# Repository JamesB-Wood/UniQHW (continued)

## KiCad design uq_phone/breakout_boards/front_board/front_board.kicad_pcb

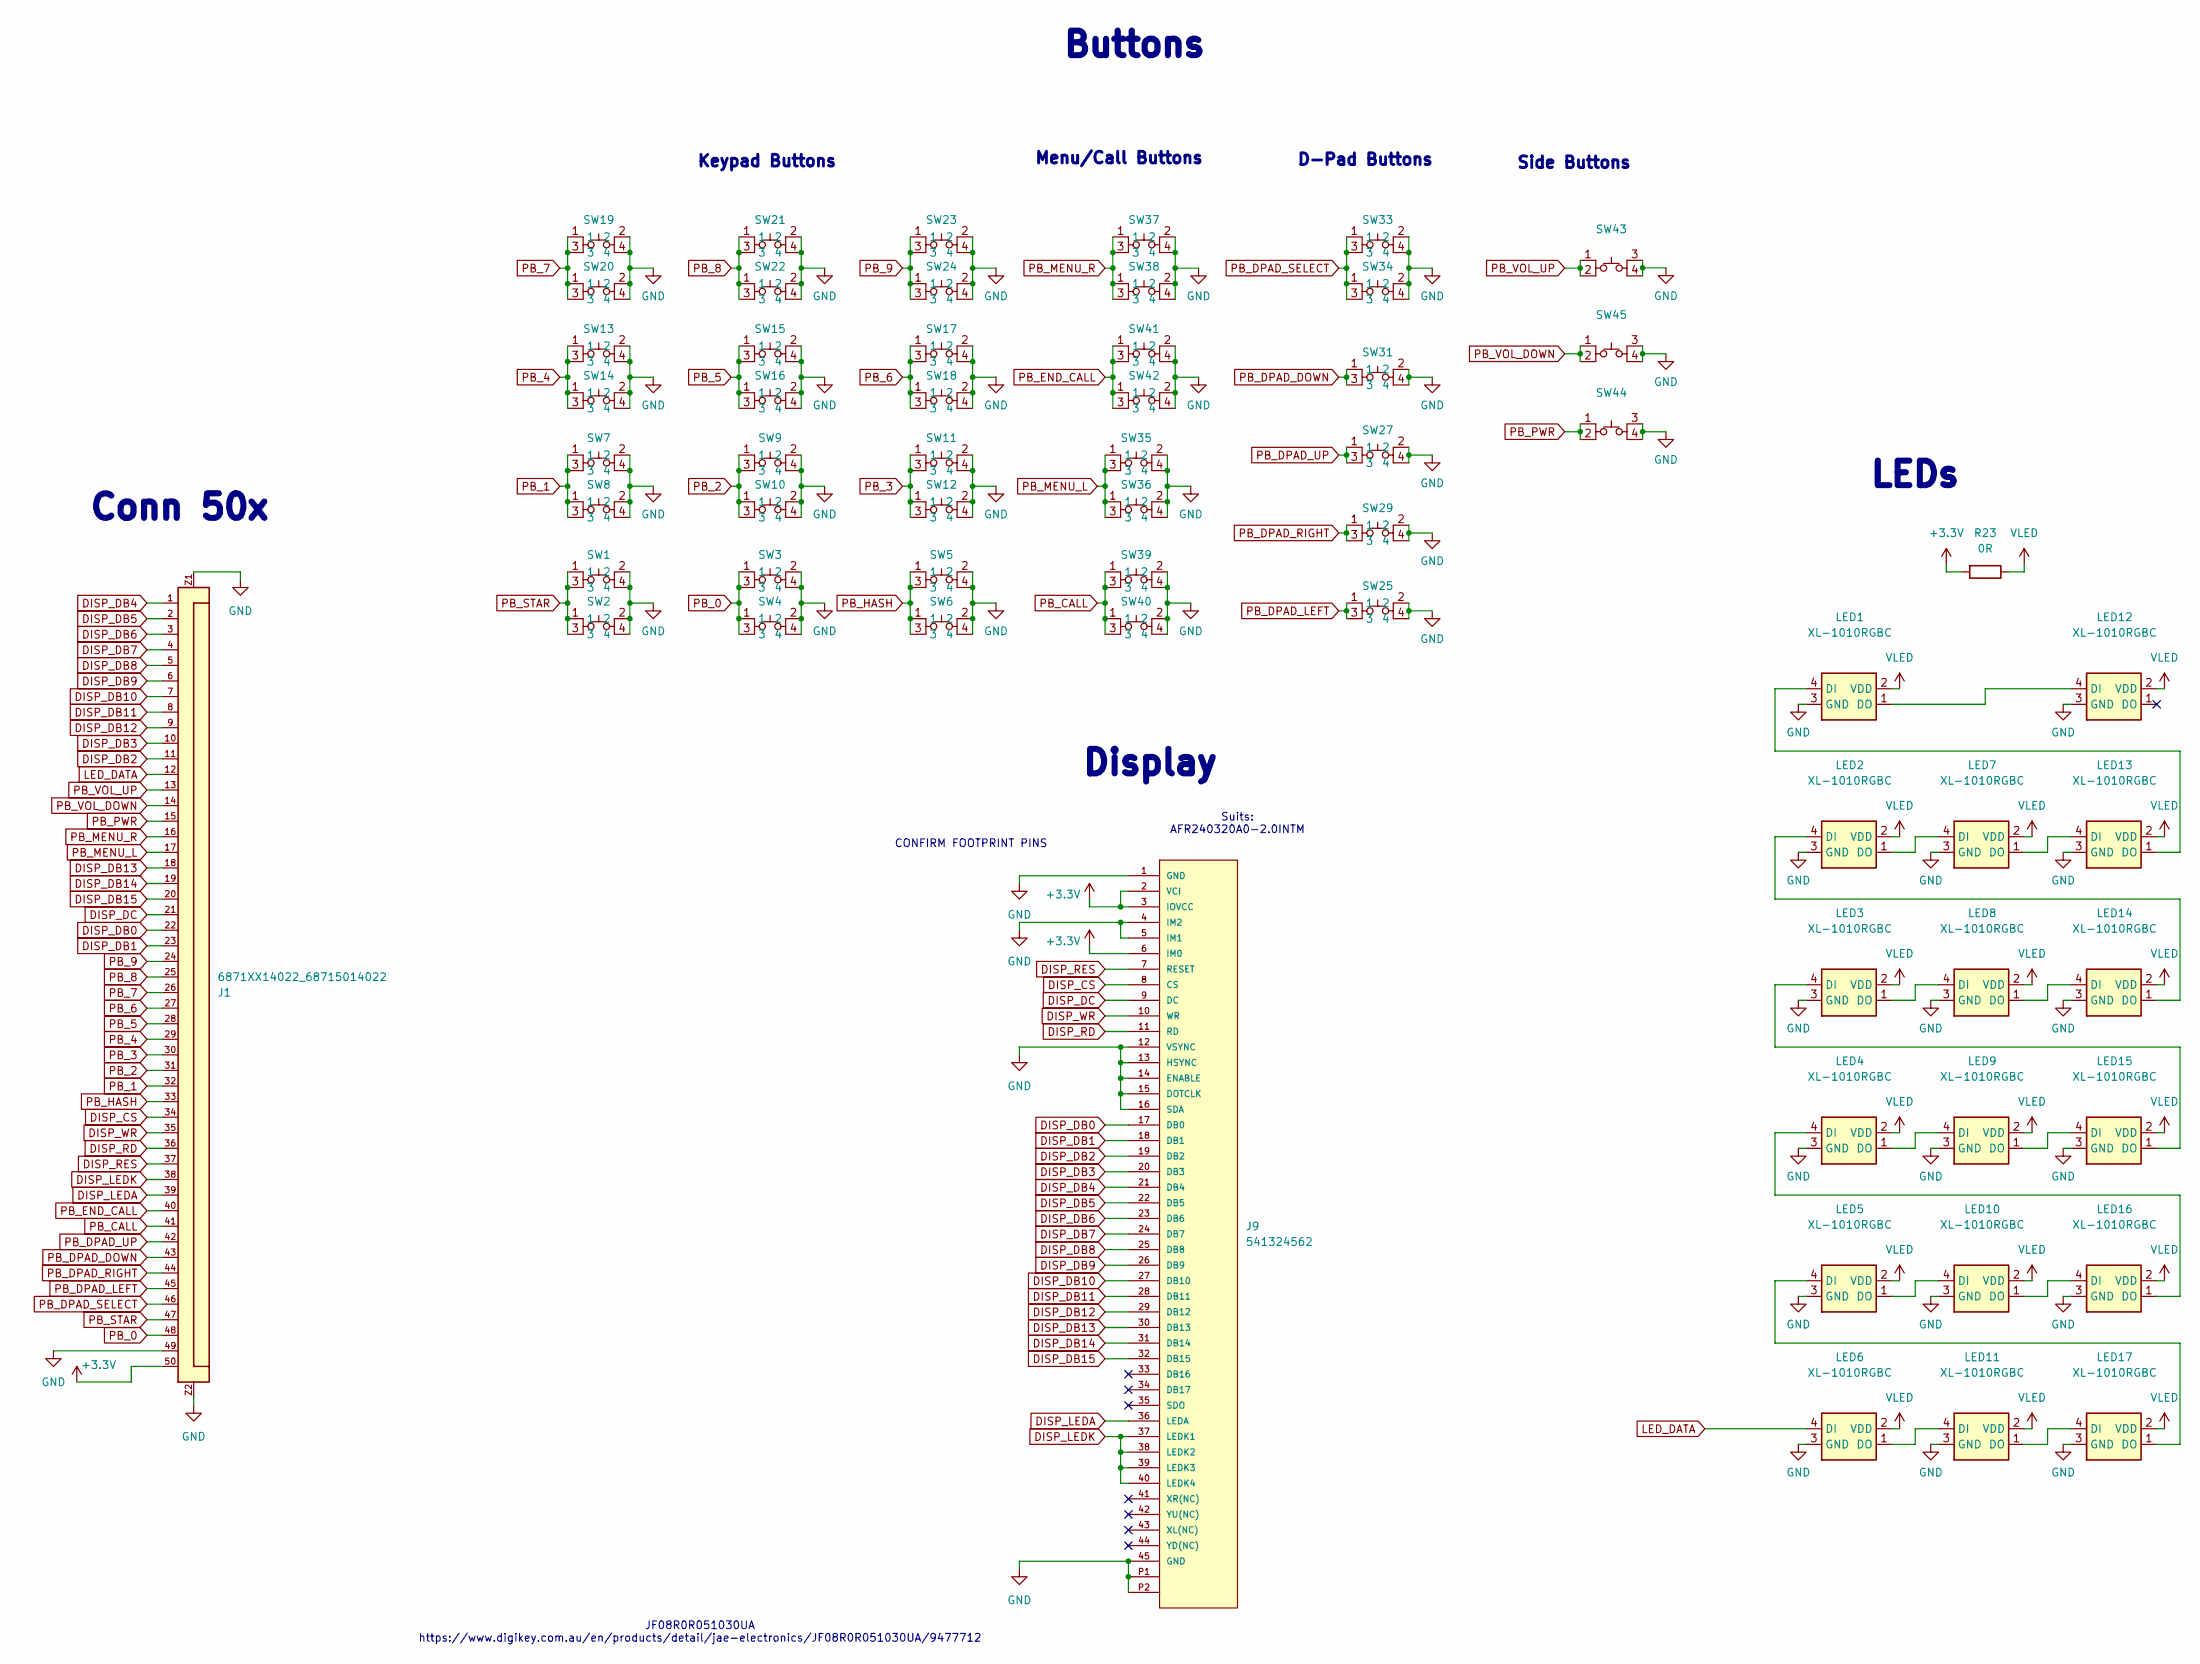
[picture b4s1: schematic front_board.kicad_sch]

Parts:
J1: 6871XX14022_68715014022; 68715014022
J9: 541324562; CON_541324562_MOL; MANUFACTURER_PART_NUMBER 541324562; DigiKey_Part_Number WM8850TR-ND
LED1, LED2, LED3, LED4, LED5, LED6, LED7, LED8, LED9, LED10, LED11, LED12, LED13, LED14, LED15, LED16, LED17: XL-1010RGBC; XL-1010RGBC-WS2812B; LCSC PN C5349953
R23: 0R; R_0603_1608Metric
SW1, SW2, SW3, SW4, SW5, SW6, SW7, SW8, SW9, SW10, SW11, SW12, SW13, SW14, SW15, SW16, SW17, SW18, SW19, SW20, SW21, SW22, SW23, SW24, SW25, SW27, SW29, SW31, SW33, SW34, SW35, SW36, SW37, SW38, SW39, SW40, SW41, SW42: SKTAAAE010; LCSC PN C358616
SW43, SW44, SW45: SKSCLCE010; LCSC PN C139799

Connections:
+3.3V: J1.50, J9.2 (VCI), J9.3 (IOVCC), J9.6 (IM0), R23.2
DISP_CS: J1.34, J9.8 (CS)
DISP_DB0: J1.22, J9.17 (DB0)
DISP_DB1: J1.23, J9.18 (DB1)
DISP_DB2: J1.11, J9.19 (DB2)
DISP_DB3: J1.10, J9.20 (DB3)
DISP_DB4: J1.1, J9.21 (DB4)
DISP_DB5: J1.2, J9.22 (DB5)
DISP_DB6: J1.3, J9.23 (DB6)
DISP_DB7: J1.4, J9.24 (DB7)
DISP_DB8: J1.5, J9.25 (DB8)
DISP_DB9: J1.6, J9.26 (DB9)
DISP_DB10: J1.7, J9.27 (DB10)
DISP_DB11: J1.8, J9.28 (DB11)
DISP_DB12: J1.9, J9.29 (DB12)
DISP_DB13: J1.18, J9.30 (DB13)
DISP_DB14: J1.19, J9.31 (DB14)
DISP_DB15: J1.20, J9.32 (DB15)
DISP_DC: J1.21, J9.9 (DC)
DISP_LEDA: J1.39, J9.36 (LEDA)
DISP_LEDK: J1.38, J9.37 (LEDK1), J9.38 (LEDK2), J9.39 (LEDK3), J9.40 (LEDK4)
DISP_RD: J1.36, J9.11 (RD)
DISP_RES: J1.37, J9.7 (RESET)
DISP_WR: J1.35, J9.10 (WR)
GND: J1.49, J1.Z1, J1.Z2, J9.1 (GND), J9.4 (IM2), J9.5 (IM1), J9.12 (VSYNC), J9.13 (HSYNC), J9.14 (ENABLE), J9.15 (DOTCLK), J9.16 (SDA), J9.45 (GND), J9.P1, J9.P2, LED1.3 (GND), LED2.3 (GND), LED3.3 (GND), LED4.3 (GND), LED5.3 (GND), LED6.3 (GND), LED7.3 (GND), LED8.3 (GND), LED9.3 (GND), LED10.3 (GND), LED11.3 (GND), LED12.3 (GND), LED13.3 (GND), LED14.3 (GND), LED15.3 (GND), LED16.3 (GND), LED17.3 (GND), SW1.2, SW1.4, SW2.2, SW2.4, SW3.2, SW3.4, SW4.2, SW4.4, SW5.2, SW5.4, SW6.2, SW6.4, SW7.2, SW7.4, SW8.2, SW8.4, SW9.2, SW9.4, SW10.2, SW10.4, SW11.2, SW11.4, SW12.2, SW12.4, SW13.2, SW13.4, SW14.2, SW14.4, SW15.2, SW15.4, SW16.2, SW16.4, SW17.2, SW17.4, SW18.2, SW18.4, SW19.2, SW19.4, SW20.2, SW20.4, SW21.2, SW21.4, SW22.2, SW22.4, SW23.2, SW23.4, SW24.2, SW24.4, SW25.2, SW25.4, SW27.2, SW27.4, SW29.2, SW29.4, SW31.2, SW31.4, SW33.2, SW33.4, SW34.2, SW34.4, SW35.2, SW35.4, SW36.2, SW36.4, SW37.2, SW37.4, SW38.2, SW38.4, SW39.2, SW39.4, SW40.2, SW40.4, SW41.2, SW41.4, SW42.2, SW42.4, SW43.3, SW43.4, SW44.3, SW44.4, SW45.3, SW45.4
LED_DATA: J1.12, LED6.4 (DI)
unnamed: LED1.4 (DI), LED13.1 (DO)
unnamed: LED1.1 (DO), LED12.4 (DI)
unnamed: LED2.1 (DO), LED7.4 (DI)
unnamed: LED3.1 (DO), LED8.4 (DI)
unnamed: LED4.1 (DO), LED9.4 (DI)
unnamed: LED5.1 (DO), LED10.4 (DI)
unnamed: LED10.1 (DO), LED16.4 (DI)
unnamed: LED6.1 (DO), LED11.4 (DI)
unnamed: LED11.1 (DO), LED17.4 (DI)
unnamed: LED7.1 (DO), LED13.4 (DI)
unnamed: LED8.1 (DO), LED14.4 (DI)
unnamed: LED2.4 (DI), LED14.1 (DO)
unnamed: LED9.1 (DO), LED15.4 (DI)
unnamed: LED3.4 (DI), LED15.1 (DO)
unnamed: LED4.4 (DI), LED16.1 (DO)
unnamed: LED5.4 (DI), LED17.1 (DO)
PB_0: J1.48, SW3.1, SW3.3, SW4.1, SW4.3
PB_1: J1.32, SW7.1, SW7.3, SW8.1, SW8.3
PB_2: J1.31, SW9.1, SW9.3, SW10.1, SW10.3
PB_3: J1.30, SW11.1, SW11.3, SW12.1, SW12.3
PB_4: J1.29, SW13.1, SW13.3, SW14.1, SW14.3
PB_5: J1.28, SW15.1, SW15.3, SW16.1, SW16.3
PB_6: J1.27, SW17.1, SW17.3, SW18.1, SW18.3
PB_7: J1.26, SW19.1, SW19.3, SW20.1, SW20.3
PB_8: J1.25, SW21.1, SW21.3, SW22.1, SW22.3
PB_9: J1.24, SW23.1, SW23.3, SW24.1, SW24.3
PB_CALL: J1.41, SW39.1, SW39.3, SW40.1, SW40.3
PB_DPAD_DOWN: J1.43, SW31.1, SW31.3
PB_DPAD_LEFT: J1.45, SW25.1, SW25.3
PB_DPAD_RIGHT: J1.44, SW29.1, SW29.3
PB_DPAD_SELECT: J1.46, SW33.1, SW33.3, SW34.1, SW34.3
PB_DPAD_UP: J1.42, SW27.1, SW27.3
PB_END_CALL: J1.40, SW41.1, SW41.3, SW42.1, SW42.3
PB_HASH: J1.33, SW5.1, SW5.3, SW6.1, SW6.3
PB_MENU_L: J1.17, SW35.1, SW35.3, SW36.1, SW36.3
PB_MENU_R: J1.16, SW37.1, SW37.3, SW38.1, SW38.3
PB_PWR: J1.15, SW44.1, SW44.2
PB_STAR: J1.47, SW1.1, SW1.3, SW2.1, SW2.3
PB_VOL_DOWN: J1.14, SW45.1, SW45.2
PB_VOL_UP: J1.13, SW43.1, SW43.2
VLED: LED1.2 (VDD), LED2.2 (VDD), LED3.2 (VDD), LED4.2 (VDD), LED5.2 (VDD), LED6.2 (VDD), LED7.2 (VDD), LED8.2 (VDD), LED9.2 (VDD), LED10.2 (VDD), LED11.2 (VDD), LED12.2 (VDD), LED13.2 (VDD), LED14.2 (VDD), LED15.2 (VDD), LED16.2 (VDD), LED17.2 (VDD), R23.1

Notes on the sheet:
D-Pad Buttons
CONFIRM FOOTPRINT PINS
Menu/Call Buttons
Conn 50x
Keypad Buttons
LEDs
Buttons
JF08R0R051030UA https://www.digikey.com.au/en/products/detail/jae-electronics/JF08R0R051030UA/9477712
Side Buttons
Suits: AFR240320A0-2.0INTM
Display

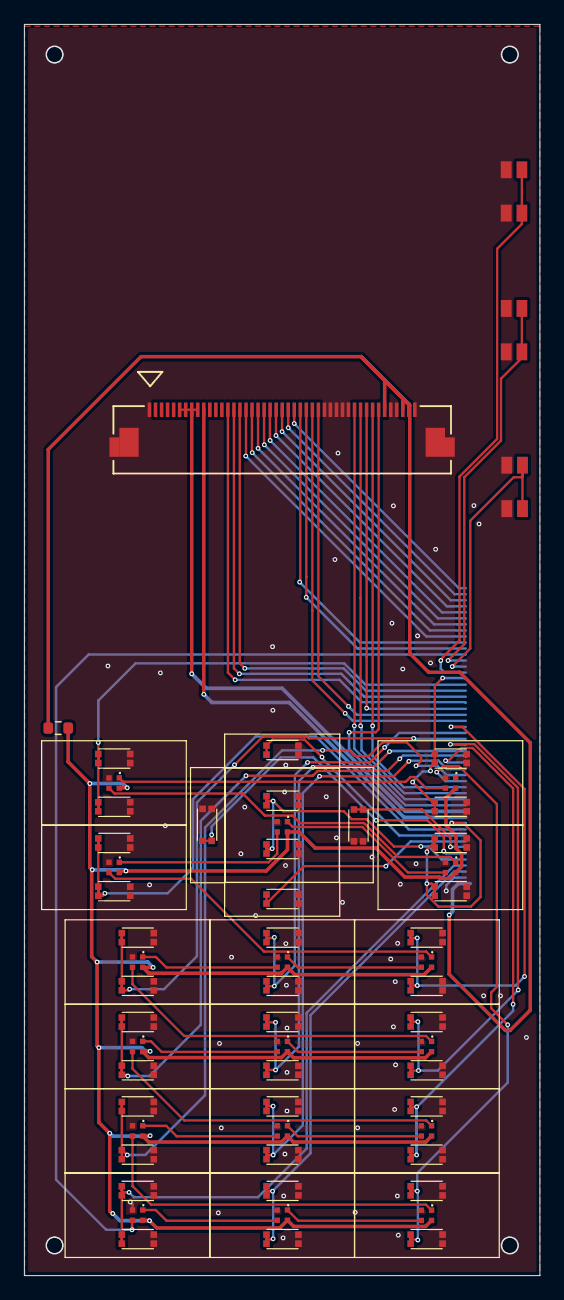
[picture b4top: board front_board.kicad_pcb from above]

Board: 2 copper layers, 42.8 x 103.7 mm, 61 parts (1 on the bottom side), 67 nets.

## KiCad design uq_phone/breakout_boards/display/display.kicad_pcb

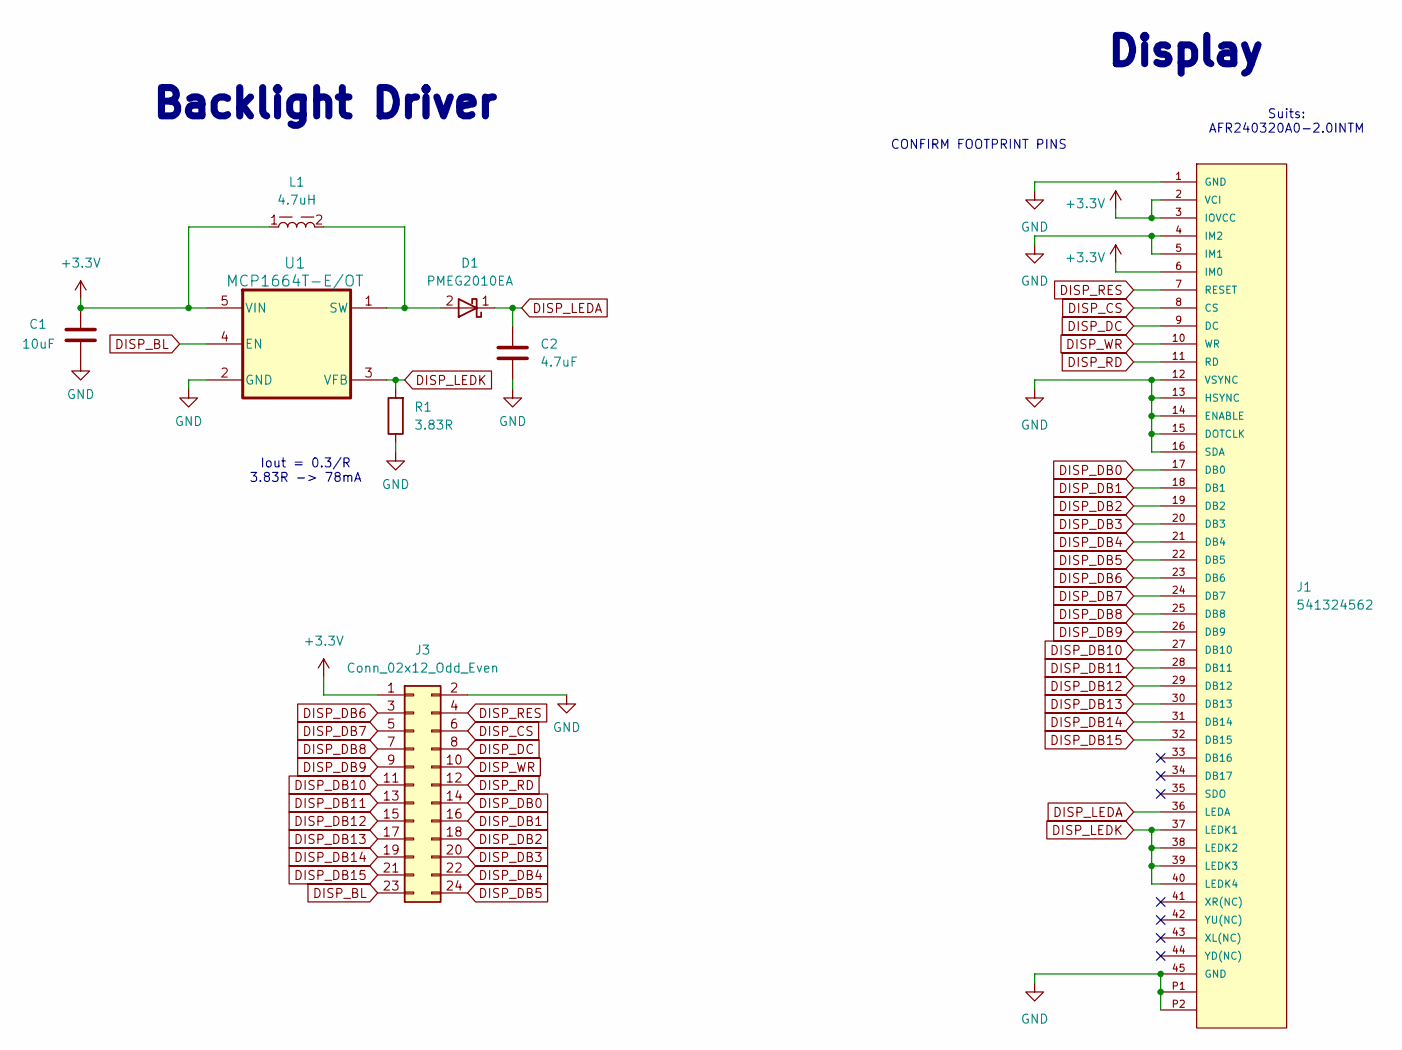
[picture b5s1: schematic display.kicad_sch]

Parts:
C1: 10uF; C_0603_1608Metric
C2: 4.7uF; C_0402_1005Metric
D1: PMEG2010EA; D_SOD-323
J1: 541324562; CON_541324562_MOL; MANUFACTURER_PART_NUMBER 541324562; DigiKey_Part_Number WM8850TR-ND
J3: Conn_02x12_Odd_Even; PinSocket_2x12_P2.54mm_Vertical
L1: 4.7uH; WE-MAPI_3015; DigiKey_Part_Number 732-4866-2-ND
R1: 3.83R; R_0603_1608Metric
U1: MCP1664T-E/OT; SOT-23-5_OT_MCH

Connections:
+3.3V: C1.1, J1.2 (VCI), J1.3 (IOVCC), J1.6 (IM0), J3.1, L1.1, U1.5 (VIN); also elsewhere on the board
DISP_BL: J3.23, U1.4 (EN)
DISP_CS: J1.8 (CS), J3.6; also elsewhere on the board
DISP_DB0: J1.17 (DB0), J3.14; also elsewhere on the board
DISP_DB1: J1.18 (DB1), J3.16; also elsewhere on the board
DISP_DB2: J1.19 (DB2), J3.18; also elsewhere on the board
DISP_DB3: J1.20 (DB3), J3.20; also elsewhere on the board
DISP_DB4: J1.21 (DB4), J3.22; also elsewhere on the board
DISP_DB5: J1.22 (DB5), J3.24; also elsewhere on the board
DISP_DB6: J1.23 (DB6), J3.3; also elsewhere on the board
DISP_DB7: J1.24 (DB7), J3.5; also elsewhere on the board
DISP_DB8: J1.25 (DB8), J3.7; also elsewhere on the board
DISP_DB9: J1.26 (DB9), J3.9; also elsewhere on the board
DISP_DB10: J1.27 (DB10), J3.11; also elsewhere on the board
DISP_DB11: J1.28 (DB11), J3.13; also elsewhere on the board
DISP_DB12: J1.29 (DB12), J3.15; also elsewhere on the board
DISP_DB13: J1.30 (DB13), J3.17; also elsewhere on the board
DISP_DB14: J1.31 (DB14), J3.19; also elsewhere on the board
DISP_DB15: J1.32 (DB15), J3.21; also elsewhere on the board
DISP_DC: J1.9 (DC), J3.8; also elsewhere on the board
DISP_LEDA: C2.1, D1.1 (K), J1.36 (LEDA); also elsewhere on the board
DISP_LEDK: J1.37 (LEDK1), J1.38 (LEDK2), J1.39 (LEDK3), J1.40 (LEDK4), R1.2, U1.3 (VFB); also elsewhere on the board
DISP_RD: J1.11 (RD), J3.12; also elsewhere on the board
DISP_RES: J1.7 (RESET), J3.4; also elsewhere on the board
DISP_WR: J1.10 (WR), J3.10; also elsewhere on the board
GND: C1.2, C2.2, J1.1 (GND), J1.4 (IM2), J1.5 (IM1), J1.12 (VSYNC), J1.13 (HSYNC), J1.14 (ENABLE), J1.15 (DOTCLK), J1.16 (SDA), J1.45 (GND), J1.P1, J1.P2, J3.2, R1.1, U1.2 (GND); also elsewhere on the board
unnamed: D1.2 (A), L1.2, U1.1 (SW)

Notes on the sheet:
Backlight Driver
CONFIRM FOOTPRINT PINS
Display
Suits: AFR240320A0-2.0INTM
Iout = 0.3/R 3.83R -> 78mA

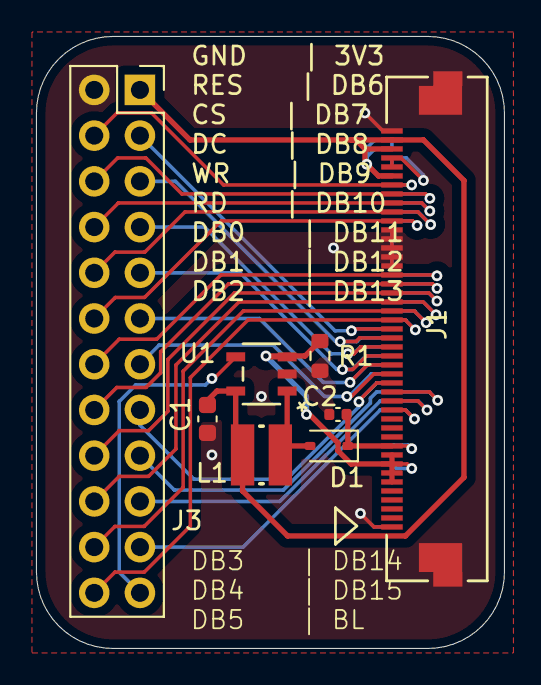
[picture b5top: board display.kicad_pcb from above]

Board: 2 copper layers, 26.0 x 34.0 mm, 9 parts (1 on the bottom side), 27 nets.

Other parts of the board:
J2: 541324562; CON_541324562_MOL

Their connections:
+3.3V: J2.40 (LEDK4), J2.43 (XL(NC)), J2.44 (YD(NC)); also elsewhere on the board
DISP_CS: J2.38 (LEDK2); also elsewhere on the board
DISP_DB0: J2.29 (DB12); also elsewhere on the board
DISP_DB1: J2.28 (DB11); also elsewhere on the board
DISP_DB2: J2.27 (DB10); also elsewhere on the board
DISP_DB3: J2.26 (DB9); also elsewhere on the board
DISP_DB4: J2.25 (DB8); also elsewhere on the board
DISP_DB5: J2.24 (DB7); also elsewhere on the board
DISP_DB6: J2.23 (DB6); also elsewhere on the board
DISP_DB7: J2.22 (DB5); also elsewhere on the board
DISP_DB8: J2.21 (DB4); also elsewhere on the board
DISP_DB9: J2.20 (DB3); also elsewhere on the board
DISP_DB10: J2.19 (DB2); also elsewhere on the board
DISP_DB11: J2.18 (DB1); also elsewhere on the board
DISP_DB12: J2.17 (DB0); also elsewhere on the board
DISP_DB13: J2.16 (SDA); also elsewhere on the board
DISP_DB14: J2.15 (DOTCLK); also elsewhere on the board
DISP_DB15: J2.14 (ENABLE); also elsewhere on the board
DISP_DC: J2.37 (LEDK1); also elsewhere on the board
DISP_LEDA: J2.10 (WR); also elsewhere on the board
DISP_LEDK: J2.6 (IM0), J2.7 (RESET), J2.8 (CS), J2.9 (DC); also elsewhere on the board
DISP_RD: J2.35 (SDO); also elsewhere on the board
DISP_RES: J2.39 (LEDK3); also elsewhere on the board
DISP_WR: J2.36 (LEDA); also elsewhere on the board
GND: J2.1 (GND), J2.30 (DB13), J2.31 (DB14), J2.32 (DB15), J2.33 (DB16), J2.34 (DB17), J2.41 (XR(NC)), J2.42 (YU(NC)), J2.45 (GND), J2.P1, J2.P2; also elsewhere on the board

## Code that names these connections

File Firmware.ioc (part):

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Mcu.Name=STM32H730VBTx
Mcu.Package=LQFP100
Mcu.UserName=STM32H730VBTx
PA10.Mode=Asynchronous
PA10.Signal=USART1_RX
PA11.Mode=CTS_RTS
PA11.Signal=USART1_CTS
PA12.Mode=CTS_RTS
PA12.Signal=USART1_RTS
PA13(JTMS/SWDIO).Mode=Serial_Wire
PA13(JTMS/SWDIO).Signal=DEBUG_JTMS-SWDIO
PA14(JTCK/SWCLK).Mode=Serial_Wire
PA14(JTCK/SWCLK).Signal=DEBUG_JTCK-SWCLK
PA3.GPIOParameters=GPIO_Label
PA3.GPIO_Label=RGB_DATA
PA3.Signal=S_TIM5_CH4
PA4.Mode=Half_Duplex_Master_Tx
PA4.Signal=I2S1_WS
PA5.Mode=Half_Duplex_Master_Tx
PA5.Signal=I2S1_CK
PA6.GPIOParameters=GPIO_Label
PA6.GPIO_Label=VIB_PWM
PA6.Signal=S_TIM3_CH1
PA7.Mode=Half_Duplex_Master_Tx
PA7.Signal=I2S1_SDO
PA8.GPIOParameters=GPIO_Label
PA8.GPIO_Label=UART_DSR
PA8.Signal=GPIO_Input
PA9.Mode=Asynchronous
PA9.Signal=USART1_TX
PB0.GPIOParameters=PinState,GPIO_Label
PB0.GPIO_Label=AUD_SW
PB0.PinState=GPIO_PIN_SET
PB0.Signal=GPIO_Output
PB1.GPIOParameters=GPIO_Label
PB1.GPIO_Label=MOB_WAKE
PB1.Signal=GPIO_Input
PB10.GPIOParameters=GPIO_Label
PB10.GPIO_Label=DISP_BL
PB10.Signal=S_TIM2_CH3
PB11.GPIOParameters=GPIO_Label
PB11.GPIO_Label=MOB_RST
PB11.Signal=GPIO_Output
PB12.GPIOParameters=GPIO_Label
PB12.GPIO_Label=FUEL_GPOUT
PB12.Signal=GPIO_Input
PB13.GPIOParameters=GPIO_Label
PB13.GPIO_Label=MCP_PG
PB13.Signal=GPIO_Input
PB14.GPIOParameters=GPIO_Label
PB14.GPIO_Label=MCP_STAT2
PB14.Signal=GPIO_Input
PB15.GPIOParameters=GPIO_Label
PB15.GPIO_Label=MCP_STAT1
PB15.Signal=GPIO_Input
PB2.GPIOParameters=GPIO_Label
PB2.GPIO_Label=MOB_PWR
PB2.Signal=GPIO_Output
PB8.Mode=I2C
PB8.Signal=I2C1_SCL
PB9.Mode=I2C
PB9.Signal=I2C1_SDA
PC10.Mode=SD_4_bits_Wide_bus
PC10.Signal=SDMMC1_D2
PC11.Mode=SD_4_bits_Wide_bus
PC11.Signal=SDMMC1_D3
PC12.Mode=SD_4_bits_Wide_bus
PC12.Signal=SDMMC1_CK
PC4.GPIOParameters=GPIO_Label
PC4.GPIO_Label=VIB_EN
PC4.Signal=GPIO_Output
PC5.GPIOParameters=GPIO_Label
PC5.GPIO_Label=HP_DET
PC5.Signal=GPIO_Input
PC6.GPIOParameters=GPIO_Label
PC6.GPIO_Label=UART_RI
PC6.Signal=GPIO_Input
PC7.GPIOParameters=GPIO_Label
PC7.GPIO_Label=SDMMC_DET
PC7.Signal=GPIO_Input
PC8.Mode=SD_4_bits_Wide_bus
PC8.Signal=SDMMC1_D0
PC9.Mode=SD_4_bits_Wide_bus
PC9.Signal=SDMMC1_D1
PD0.GPIOParameters=GPIO_Label
PD0.GPIO_Label=DISP_D2
PD0.Signal=FMC_D2_DA2
PD1.GPIOParameters=GPIO_Label
PD1.GPIO_Label=DISP_D3
PD1.Signal=FMC_D3_DA3
PD10.GPIOParameters=GPIO_Label
PD10.GPIO_Label=DISP_D15
PD10.Signal=FMC_D15_DA15
PD11.GPIOParameters=GPIO_Label
PD11.GPIO_Label=DISP_DC
PD11.Signal=FMC_A16_CLE
PD12.GPIOParameters=GPIO_Label
PD12.GPIO_Label=UART_DCD
PD12.Signal=GPIO_Input
PD13.GPIOParameters=GPIO_Label
PD13.GPIO_Label=UART_DTR
PD13.Signal=GPIO_Output
PD14.GPIOParameters=GPIO_Label
PD14.GPIO_Label=DISP_D0
PD14.Signal=FMC_D0_DA0
PD15.GPIOParameters=GPIO_Label
PD15.GPIO_Label=DISP_D1
PD15.Signal=FMC_D1_DA1
PD2.Mode=SD_4_bits_Wide_bus
PD2.Signal=SDMMC1_CMD
PD3.GPIOParameters=PinState,GPIO_PuPd,GPIO_Label
PD3.GPIO_Label=DISP_RES
PD3.GPIO_PuPd=GPIO_NOPULL
PD3.PinState=GPIO_PIN_SET
PD3.Signal=GPIO_Output
PD4.GPIOParameters=GPIO_Label
PD4.GPIO_Label=DISP_RD
PD4.Signal=FMC_NOE
PD5.GPIOParameters=GPIO_Label
PD5.GPIO_Label=DISP_WR
PD5.Signal=FMC_NWE
PD7.GPIOParameters=GPIO_Label
PD7.GPIO_Label=DISP_CS
PD7.Mode=NorPsramChipSelect1_1
PD7.Signal=FMC_NE1
PD8.GPIOParameters=GPIO_Label
PD8.GPIO_Label=DISP_D13
PD8.Signal=FMC_D13_DA13
PD9.GPIOParameters=GPIO_Label
PD9.GPIO_Label=DISP_D14
PD9.Signal=FMC_D14_DA14
PE10.GPIOParameters=GPIO_Label
PE10.GPIO_Label=DISP_D7
PE10.Signal=FMC_D7_DA7
PE11.GPIOParameters=GPIO_Label
PE11.GPIO_Label=DISP_D8
PE11.Signal=FMC_D8_DA8
PE12.GPIOParameters=GPIO_Label
PE12.GPIO_Label=DISP_D9
PE12.Signal=FMC_D9_DA9
PE13.GPIOParameters=GPIO_Label
PE13.GPIO_Label=DISP_D10
PE13.Signal=FMC_D10_DA10
PE14.GPIOParameters=GPIO_Label
PE14.GPIO_Label=DISP_D11
PE14.Signal=FMC_D11_DA11
PE15.GPIOParameters=GPIO_Label
PE15.GPIO_Label=DISP_D12
PE15.Signal=FMC_D12_DA12
PE7.GPIOParameters=GPIO_Label
PE7.GPIO_Label=DISP_D4
PE7.Signal=FMC_D4_DA4
PE8.GPIOParameters=GPIO_Label
PE8.GPIO_Label=DISP_D5
PE8.Signal=FMC_D5_DA5
PE9.GPIOParameters=GPIO_Label
PE9.GPIO_Label=DISP_D6
PE9.Signal=FMC_D6_DA6
RCC.SYSCLKFreq_VALUE=64000000
board=custom

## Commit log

2025-04-03 Upload Initial Files
2025-04-08 Update LCD, Add Programer, Shrink Footprints
2025-04-09 Shrink More footprints, rearragment of PCB
2025-04-11 Add display board
2025-04-11 Update Display Board
2025-04-11 Update PCB, minor changes
2025-04-13 Minor changes to display
2025-04-13 Changed SIM/uSD port & adjust routing
2025-04-15 Update display
2025-04-15 Arrange PCB
2025-04-15 Add gerbers
2025-04-18 Add LEDs, Inital Buttons
2025-04-19 Routing Init
2025-04-20 Update routing
2025-04-20 Update to Kicad 9.0, Add 3d Models
2025-04-22 Update pcb and remove Stm32 profile
2025-04-23 Update Keypad
2025-04-26 Add Front Pannel Suboard and connector
2025-04-26 move button outlines to silkscreen
2025-05-05 Change MCU to h733VG
2025-05-05 Swap RX TX
2025-05-08 Clean up and add DNP
2025-05-20 Minor changes
2025-05-26 Update Various Connectors
2025-05-27 Generate Early production outputs
2025-05-27 Fix outputs
2025-05-29 Update folder structure
2025-06-23 Clean repo
2025-06-29 Add more footprints, reduce sizes
2025-06-30 Various Changes to footprints and components
2025-07-13 Minor Changes - new display
2025-07-17 New HP jack, move stuff out for new arrangement
2025-08-01 New Layout
2025-08-06 Update layout and BL control
2025-08-07 Several Hours of Routing
2025-08-08 More routing and placements
2025-08-09 Another day of routing and adding components
2025-08-10 More routing and moving cellular to new project
2025-08-10 Most routing complete
2025-08-12 More roting and vias
2025-08-15 DRC and routing fixing
2025-08-17 New HP jack and circuit
2025-08-20 Restructure, route and add flex pcb
2025-08-21 New logic level shifters
2025-08-21 Add GNSS antenna for sag
2025-08-22 Fixed display pinout
2025-08-25 Routing improvements
2025-08-29 Routing Update
2025-09-11 Cleaning up adn fixing massive mistake
2025-11-28 Add Licence
2025-11-28 Rename LICENSE file to LICENCE
2025-12-04 minor comments
